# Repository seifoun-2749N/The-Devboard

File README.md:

# The-Devboard

---

# Overview:

A custom DevBoard inspired from the RP2040 devboard. Made with the same specs but in a creative way and beautiful design theme following the guide from Stasis HackClub event.

I simply choosed to make this project because I see that I can learn a lot from it since I'm dealing with small components on a tiny surafce and It will better help me understanding the working process of a DevBoard.

---

# 3D Overview :
## Front View

## Rear View

## Schematics

---

# BOM :

| Id | Designator                          | Footprint                                         | Quantity | Comment                     | Datasheet                                                                                                                                                                                                        |
| -- | ----------------------------------- | ------------------------------------------------- | -------- | --------------------------- | ---------------------------------------------------------------------------------------------------------------------------------------------------------------------------------------------------------------- |
| 1  | C1,C10                              | Capacitor_SMD:C_0402_1005Metric                   | 2        | 1uF                         | ~                                                                                                                                                                                                                |
| 2  | C2,C3,C4,C5,C6,C7,C8,C9,C11,C12,C17 | Capacitor_SMD:C_0402_1005Metric                   | 11       | 0.1uF                       | ~                                                                                                                                                                                                                |
| 3  | C13,C14                             | Capacitor_SMD:C_0603_1608Metric                   | 2        | 10uF                        | ~                                                                                                                                                                                                                |
| 4  | C15,C16                             | Capacitor_SMD:C_0402_1005Metric                   | 2        | 33pF                        | ~                                                                                                                                                                                                                |
| 5  | J1                                  | Connector_USB:USB_C_Receptacle_HRO_TYPE-C-31-M-12 | 1        | USB_C_Receptacle_USB2.0_14P | [https://www.usb.org/sites/default/files/documents/usb_type-c.zip](https://www.usb.org/sites/default/files/documents/usb_type-c.zip)                                                                             |
| 6  | L1                                  | Inductor_SMD:L_0603_1608Metric                    | 1        | 10uH                        | ~                                                                                                                                                                                                                |
| 7  | R1                                  | Resistor_SMD:R_0402_1005Metric                    | 1        | 5.1k                        | ~                                                                                                                                                                                                                |
| 8  | R2                                  | Resistor_SMD:R_0402_1005Metric                    | 1        | 10k                         | ~                                                                                                                                                                                                                |
| 9  | R3                                  | Resistor_SMD:R_0402_1005Metric                    | 1        | 1k                          | ~                                                                                                                                                                                                                |
| 10 | SW1                                 | Button_Switch_SMD:SW_SPST_TL3342                  | 1        | RESET                       | ~                                                                                                                                                                                                                |
| 11 | U1                                  | Package_QFN:QFN-48-1EP_6x6mm_P0.4mm_EP4.4x4.4mm   | 1        | ESP32-S3-WROOM-1            | [https://www.espressif.com/sites/default/files/documentation/esp32-s3-wroom-1_wroom-1u_datasheet_en.pdf](https://www.espressif.com/sites/default/files/documentation/esp32-s3-wroom-1_wroom-1u_datasheet_en.pdf) |
| 12 | U2                                  | Package_TO_SOT_SMD:SOT-23-5                       | 1        | AMS1117-3.3                 | ~                                                                                                                                                                                                                |
| 13 | Y1                                  | Crystal:Crystal_SMD_3225-4Pin_3.2x2.5mm           | 1        | 40MHz                       | ~                                                                                                                                                                                                                |
| 14 | D1                                  | LED_SMD:LED_0603_1608Metric                       | 1        | Power LED                   | ~                                                                                                                                                                                                                |
| 15 | TP1,TP2                             | TestPoint:TestPoint_Pad_D1.0mm                    | 2        | GPIO Test Points            | ~                                                                                                                                                                                                                |
| 16 | H1,H2,H3,H4                         | MountingHole:MountingHole_2.2mm_M2                | 4        | Mounting Holes              | ~                                                                                                                                                                                                                |

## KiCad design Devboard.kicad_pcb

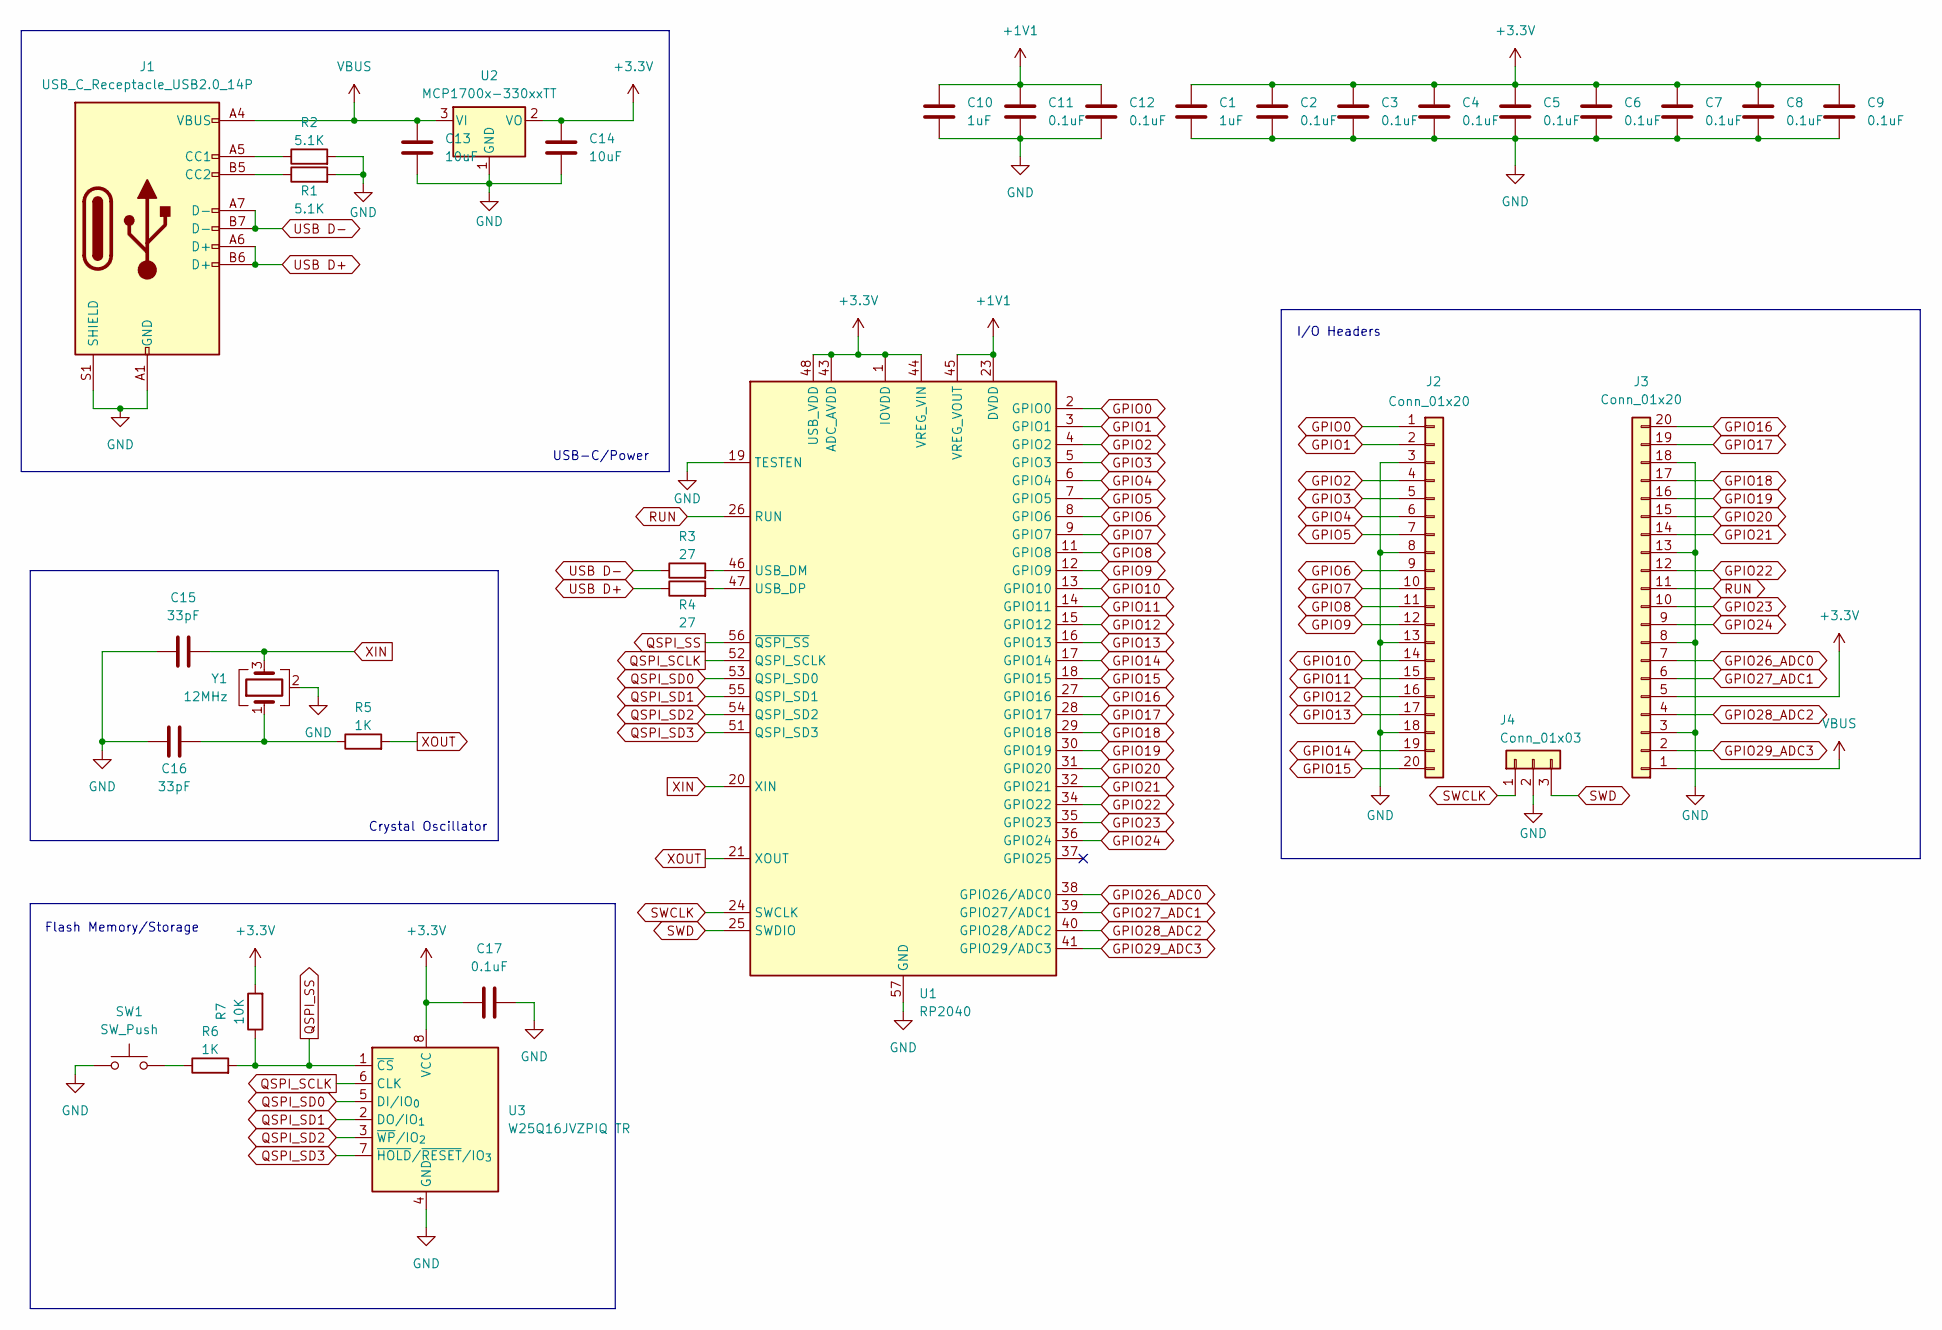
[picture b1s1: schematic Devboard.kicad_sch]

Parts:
C1, C10: 1uF; C_0402_1005Metric
C2, C3, C4, C5, C6, C7, C8, C9, C11, C12, C17: 0.1uF; C_0402_1005Metric
C13, C14: 10uF; C_0603_1608Metric
C15, C16: 33pF; C_0402_1005Metric
J1: USB_C_Receptacle_USB2.0_14P; USB_C_Receptacle_HRO_TYPE-C-31-M-12
J2, J3: Conn_01x20; PinHeader_1x20_P2.54mm_Vertical
J4: Conn_01x03; PinHeader_1x03_P2.54mm_Vertical
R1, R2: 5.1K; R_0402_1005Metric
R3, R4: 27; R_0402_1005Metric
R5, R6: 1K; R_0402_1005Metric
R7: 10K; R_0402_1005Metric
SW1: SW_Push; SW_Push_SPST_NO_Alps_SKRK
U1: RP2040; QFN-56-1EP_7x7mm_P0.4mm_EP3.2x3.2mm
U2: MCP1700x-330xxTT; SOT-23
U3: W25Q16JVZPIQ TR; Winbond_USON-8-1EP_3x2mm_P0.5mm_EP0.2x1.6mm
Y1: 12MHz; Crystal_SMD_3225-4Pin_3.2x2.5mm

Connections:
+1V1: C10.1, C11.1, C12.1, U1.23 (DVDD), U1.45 (VREG_VOUT), U1.50 (DVDD)
+3.3V: C1.1, C2.1, C3.1, C4.1, C5.1, C6.1, C7.1, C8.1, C9.1, C14.1, C17.1, J3.5, R7.2, U1.1 (IOVDD), U1.10 (IOVDD), U1.22 (IOVDD), U1.33 (IOVDD), U1.42 (IOVDD), U1.43 (ADC_AVDD), U1.44 (VREG_VIN), U1.48 (USB_VDD), U1.49 (IOVDD), U2.2 (VO), U3.8 (VCC)
GND: C1.2, C2.2, C3.2, C4.2, C5.2, C6.2, C7.2, C8.2, C9.2, C10.2, C11.2, C12.2, C13.2, C14.2, C15.1, C16.1, C17.2, J1.A1 (GND), J1.A12 (GND), J1.B1 (GND), J1.B12 (GND), J1.S1 (SHIELD), J2.3, J2.8, J2.13, J2.18, J3.3, J3.8, J3.13, J3.18, J4.2, R1.2, R2.2, SW1.1, U1.19 (TESTEN), U1.57 (GND), U2.1 (GND), U3.4 (GND), Y1.2 (G), Y1.4 (G)
GPIO0: J2.1, U1.2 (GPIO0)
GPIO1: J2.2, U1.3 (GPIO1)
GPIO2: J2.4, U1.4 (GPIO2)
GPIO3: J2.5, U1.5 (GPIO3)
GPIO4: J2.6, U1.6 (GPIO4)
GPIO5: J2.7, U1.7 (GPIO5)
GPIO6: J2.9, U1.8 (GPIO6)
GPIO7: J2.10, U1.9 (GPIO7)
GPIO8: J2.11, U1.11 (GPIO8)
GPIO9: J2.12, U1.12 (GPIO9)
GPIO10: J2.14, U1.13 (GPIO10)
GPIO11: J2.15, U1.14 (GPIO11)
GPIO12: J2.16, U1.15 (GPIO12)
GPIO13: J2.17, U1.16 (GPIO13)
GPIO14: J2.19, U1.17 (GPIO14)
GPIO15: J2.20, U1.18 (GPIO15)
GPIO16: J3.20, U1.27 (GPIO16)
GPIO17: J3.19, U1.28 (GPIO17)
GPIO18: J3.17, U1.29 (GPIO18)
GPIO19: J3.16, U1.30 (GPIO19)
GPIO20: J3.15, U1.31 (GPIO20)
GPIO21: J3.14, U1.32 (GPIO21)
GPIO22: J3.12, U1.34 (GPIO22)
GPIO23: J3.10, U1.35 (GPIO23)
GPIO24: J3.9, U1.36 (GPIO24)
GPIO26_ADC0: J3.7, U1.38 (GPIO26/ADC0)
GPIO27_ADC1: J3.6, U1.39 (GPIO27/ADC1)
GPIO28_ADC2: J3.4, U1.40 (GPIO28/ADC2)
GPIO29_ADC3: J3.2, U1.41 (GPIO29/ADC3)
unnamed: C16.2, R5.1, Y1.1
unnamed: J1.A5 (CC1), R2.1
unnamed: J1.B5 (CC2), R1.1
unnamed: R6.1, SW1.2
unnamed: R3.2, U1.46 (USB_DM)
unnamed: R4.2, U1.47 (USB_DP)
QSPI_SCLK: U1.52 (QSPI_SCLK), U3.6 (CLK)
QSPI_SD0: U1.53 (QSPI_SD0), U3.5 (DI/IO_{0})
QSPI_SD1: U1.55 (QSPI_SD1), U3.2 (DO/IO_{1})
QSPI_SD2: U1.54 (QSPI_SD2), U3.3 (~WP/IO_{2})
QSPI_SD3: U1.51 (QSPI_SD3), U3.7 (~HOLD/~RESET/IO_{3})
QSPI_SS: R6.2, R7.1, U1.56 (~QSPI_SS), U3.1 (~CS)
RUN: J3.11, U1.26 (RUN)
SWCLK: J4.1, U1.24 (SWCLK)
SWD: J4.3, U1.25 (SWDIO)
USB D+: J1.A6 (D+), J1.B6 (D+), R4.1
USB D-: J1.A7 (D-), J1.B7 (D-), R3.1
VBUS: C13.1, J1.A4 (VBUS), J1.A9 (VBUS), J1.B4 (VBUS), J1.B9 (VBUS), J3.1, U2.3 (VI)
XIN: C15.2, U1.20 (XIN), Y1.3
XOUT: R5.2, U1.21 (XOUT)

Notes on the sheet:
I/O Headers
Crystal Oscillator
Flash Memory/Storage
USB-C/Power

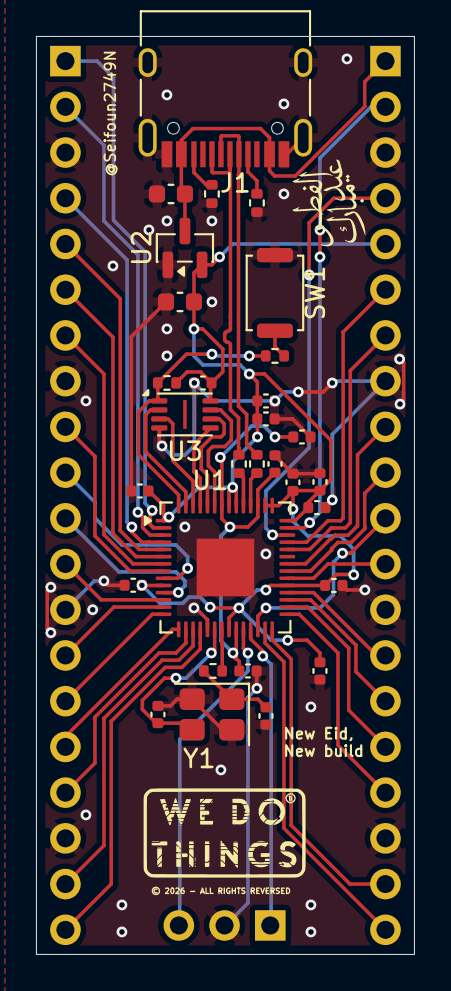
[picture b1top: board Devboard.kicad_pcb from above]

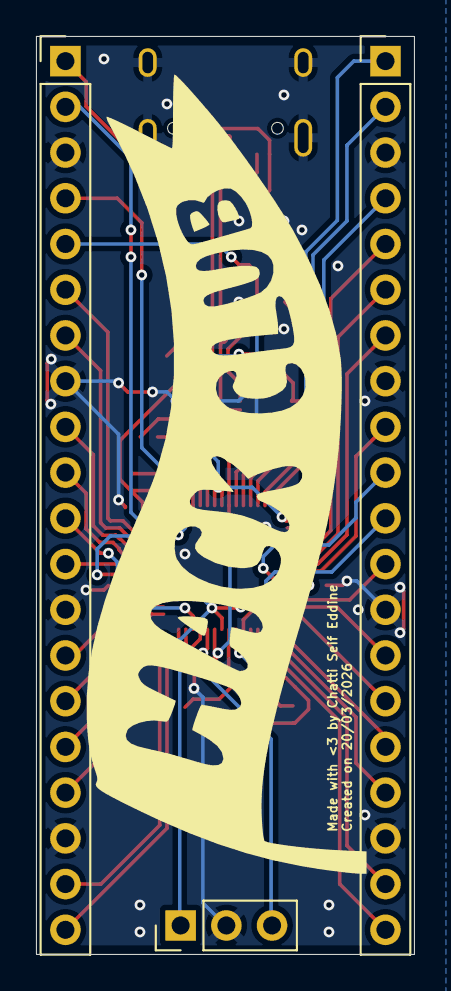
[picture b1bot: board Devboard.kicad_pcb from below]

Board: 2 copper layers, 21.0 x 51.0 mm, 33 parts (3 on the bottom side), 52 nets.

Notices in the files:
Devboard.kicad_pcb:
© 2026 - ALL RIGHTS REVERSED
